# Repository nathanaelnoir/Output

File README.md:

# Output (KiCad 9)

Multi-sheet KiCad 9 project providing schematics and PCB for audio output / amplifier modules.

## Table of contents
- Overview
- Features
- Project layout
- Quick start
- Build & assembly notes
- Testing
- BOM
- Contributing
- License

## Overview
This repository contains the KiCad 9 project `output_pcb`. It includes multiple schematic sheets (HP amp, line amp, IO, volume meter, etc.) and a single PCB layout. All design files live under `kicad/`.

## Features
- Multi-sheet schematic architecture for modular subsystems.
- Single PCB layout in KiCad 9 format: `kicad/output_pcb.kicad_pcb`.
- Mix of through-hole and SMD parts (jacks, headers, op-amps, passives).

## Project layout
Project files:
- `kicad/output_pcb.kicad_pro` — KiCad project file
- `kicad/output_pcb.kicad_sch` — top-level schematic (hierarchical)
- `kicad/output_pcb.kicad_pcb` — PCB layout
- `kicad/output_pcb.kicad_prl` — plot/print settings

- `output/` — generated zipped gerbers and other fabrication outputs

Schematic sheets:
- `kicad/hp_amp.kicad_sch` — HP / amp sheet
- `kicad/line_amp.kicad_sch` — line amp sheet
- `kicad/io_board.kicad_sch` — IO / connectors
- `kicad/rear_board.kicad_sch` — rear panel / connectors
- `kicad/volume_meter.kicad_sch` — meter sheet

## Quick start
1. Install KiCad 9.
2. Open `kicad/output_pcb.kicad_pro`.
3. In Schematic Editor: run ERC and review results.
4. In PCB Editor: update PCB from schematic, then run DRC.
5. Generate fabrication outputs (Gerbers, drill, BOM, pick-and-place) as needed.

## Build & assembly notes
- Follow footprints and polarity/orientation markings (IC notches, electrolytics, LEDs, diodes).
- Suggested assembly order: SMD (reflow/paste) → THT (jacks, headers, pots) → mechanical fixtures.
- Decoupling: place 100 nF capacitors close to each op-amp’s power pins; use bulk electrolytics on rails where appropriate.
- Verify mechanical alignment (jack positions, mounting holes) against your panel/enclosure before final tightening.

## Testing
1. Power: apply power with no signal inputs; verify rail voltages and polarity at key ICs/connectors.
2. Signal: inject known signals; verify outputs with an oscilloscope or audio probe.
3. Mechanics: confirm jack seating, connector fit, and pot operation.

## BOM
The BOM is user-maintained in `BOM.md`. A KiCad-exported CSV can be generated from the schematic if you prefer a machine-readable BOM.

<details>
  <summary><strong>Detailed BOM</strong></summary>

### Bill of Materials

Please verify against the schematic before procurement.

Sanity-check totals (deduplicated):
- Capacitors (C): 34
- Diodes/LEDs (D): 12
- Mounting holes (H): 4
- Connectors/Jacks/Headers (J): 13
- Resistors (R): 48
- Pots (RV): 2
- ICs (U): 12
- Total line-item quantity: 125

Cleanup notes:
- Removed duplicate single entries for `C1` and `C2` (the combined `C1, C2` entry already covers them).
- `U2, U7, U10–U12`: datasheet link points to TL071 (not TL074). Consider updating the URL.
- `J12, J22`: footprint name contains repeated `P2.54mm`; confirm it matches your library.

### BOM table

| Designator(s) | Qty | Value / Part | Footprint | Vendor / URL | Notes |
|---|---:|---|---|---|---|
| C1, C2 | 2 | 150 nF | Capacitor_THT:C_Disc_D4.7mm_W2.5mm_P5.00mm | https://www.taydaelectronics.com/10-x-0-15uf-50v-ceramic-disc-capacitor-pkg-of-10.html | |
| C5–C28 | 24 | 100 nF | Capacitor_THT:C_Disc_D4.7mm_W2.5mm_P5.00mm | https://www.taydaelectronics.com/a-553-0-1uf-50v-ceramic-disc-capacitor-pkg-of-10.html | |
| C29, C30, C33, C34 | 4 | 100 pF | Capacitor_THT:C_Disc_D4.7mm_W2.5mm_P5.00mm | https://www.taydaelectronics.com/10-x-100pf-50v-ceramic-disc-capacitor-pkg-of-10.html | |
| C31, C32, C39, C40 | 4 | 10 µF | Capacitor_THT:CP_Radial_D4.0mm_P1.50mm | https://www.taydaelectronics.com/datasheets/files/A-3931.PDF | |
| D1, D2 | 2 | 1N4148 | Diode_THT:D_A-405_P7.62mm_Horizontal | https://www.taydaelectronics.com/datasheets/files/A-157.PDF | |
| D3, D8 | 2 | LED (RED) 3mm | LED_THT:LED_D3.0mm_Clear | https://www.taydaelectronics.com/led-3mm-red-water-clear-ultra-bright.html | |
| D4, D9 | 2 | LED (AMBER) 3mm | LED_THT:LED_D3.0mm_Clear | https://www.taydaelectronics.com/led-3mm-orange-water-clear.html | |
| D5–D7, D10–D12 | 6 | LED (GREEN) 3mm | LED_THT:LED_D3.0mm_Clear | https://www.taydaelectronics.com/led-3mm-green-water-clear-super-bright.html | |
| H1–H4 | 4 | Mounting Hole 2.7mm | MountingHole:MountingHole_2.7mm_M2.5 | — | |
| J1, J2 | 2 | 3.5 mm Audio Jack (switching) | Eurorack:Jack_3.5mm_QingPu_WQP-PJ398SM_Vertical | https://www.taydaelectronics.com/datasheets/files/w-qp-518ma_drawings.pdf | |
| J3–J5 | 3 | 6.35 mm Audio Jack | Eurorack:Jack_6.35mm_PJ_629HAN_slots | https://www.taydaelectronics.com/datasheets/files/A-1121.pdf | |
| J6 | 1 | 2x5 Eurorack power header | Connector_IDC:IDC-Header_2x05_P2.54mm_Vertical | https://www.taydaelectronics.com/datasheets/files/A-2939.pdf | |
| J7 | 1 | 1x3 Pin Socket | Connector_PinHeader_2.54mm:PinHeader_1x03_P2.54mm_Vertical | https://www.taydaelectronics.com/datasheets/files/FH411.pdf | |
| J11, J13, J21, J23 | 4 | 1x10 Pin Header | Connector_PinHeader_2.54mm:PinHeader_1x10_P2.54mm_Vertical | https://www.taydaelectronics.com/datasheets/files/A-197.pdf | |
| J12, J22 | 2 | 1x10 Pin Socket | Connector_PinHeader_2.54mm:PinHeader_1x10_P2.54mm_P2.54mm_Vertical | https://www.taydaelectronics.com/datasheets/files/FH411.pdf | |
| R1, R2 | 2 | 100 kΩ | Resistor_THT:R_Axial_DIN0207_L6.3mm_D2.5mm_P10.16mm_Horizontal | reichelt | |
| R3, R11, R19, R20 | 4 | 20 kΩ | Resistor_THT:R_Axial_DIN0207_L6.3mm_D2.5mm_P10.16mm_Horizontal | https://www.taydaelectronics.com/datasheets/files/royalohmprecisionmetalmf.pdf | |
| R4–R6, R12–R14, R21–R26, R39–R48 | 22 | 10 kΩ | Resistor_THT:R_Axial_DIN0207_L6.3mm_D2.5mm_P10.16mm_Horizontal | https://www.taydaelectronics.com/datasheets/files/royalohmprecisionmetalmf.pdf | |
| R7–R10, R15–R18 | 8 | 10 Ω | Resistor_THT:R_Axial_DIN0207_L6.3mm_D2.5mm_P10.16mm_P10.16mm_Horizontal | reichelt | footprint string differs; verify |
| R27–R30 | 4 | 100 Ω | Resistor_THT:R_Axial_DIN0207_L6.3mm_D2.5mm_P10.16mm_Horizontal | reichelt | |
| R31, R32 | 2 | 22 kΩ | Resistor_THT:R_Axial_DIN0207_L6.3mm_D2.5mm_P10.16mm_Horizontal | reichelt | |
| R33 | 1 | 33 kΩ | Resistor_THT:R_Axial_DIN0207_L6.3mm_D2.5mm_P10.16mm_Horizontal | reichelt | |
| R34 | 1 | 2.2 kΩ | Resistor_THT:R_Axial_DIN0207_L6.3mm_D2.5mm_P10.16mm_Horizontal | reichelt | |
| R35 | 1 | 1.5 kΩ | Resistor_THT:R_Axial_DIN0207_L6.3mm_D2.5mm_P10.16mm_Horizontal | https://www.taydaelectronics.com/datasheets/files/royalohmprecisionmetalmf.pdf | |
| R36 | 1 | 2.4 kΩ | Resistor_THT:R_Axial_DIN0207_L6.3mm_D2.5mm_P10.16mm_Horizontal | https://www.taydaelectronics.com/datasheets/files/royalohmprecisionmetalmf.pdf | |
| R37 | 1 | 820 Ω | Resistor_THT:R_Axial_DIN0207_L6.3mm_D2.5mm_P10.16mm_Horizontal | https://www.taydaelectronics.com/datasheets/files/royalohmprecisionmetalmf.pdf | |
| R38 | 1 | 470 Ω | Resistor_THT:R_Axial_DIN0207_L6.3mm_D2.5mm_P10.16mm_Horizontal | reichelt | |
| RV1, RV2 | 2 | 50 kΩ B (potentiometer) | Eurorack:Potentiometer_Alpha_RD902F-40-00D_Dual_Vertical_CircularHoles_centered | https://www.taydaelectronics.com/datasheets/files/A-5440.pdf | |
| U1 | 1 | TL072 (dual op-amp) | Package_DIP:DIP-8_W7.62mm | reichelt | |
| U2, U7, U10–U12 | 5 | TL074 (quad op-amp) | Package_DIP:DIP-14_W7.62mm | http://www.ti.com/lit/ds/symlink/tl071.pdf | datasheet link likely for TL074 |
| U3–U6, U8, U9 | 6 | NE5532 (dual op-amp) | Package_DIP:DIP-8_W7.62mm | https://www.taydaelectronics.com/ne5532-5532-ic-dual-low-noise-op-amp.html | |

</details>

## Contributing
Issues and PRs welcome. If you change schematics/PCB, include updated BOM and any relevant build/test notes.

## License
MIT — see `LICENSE`.

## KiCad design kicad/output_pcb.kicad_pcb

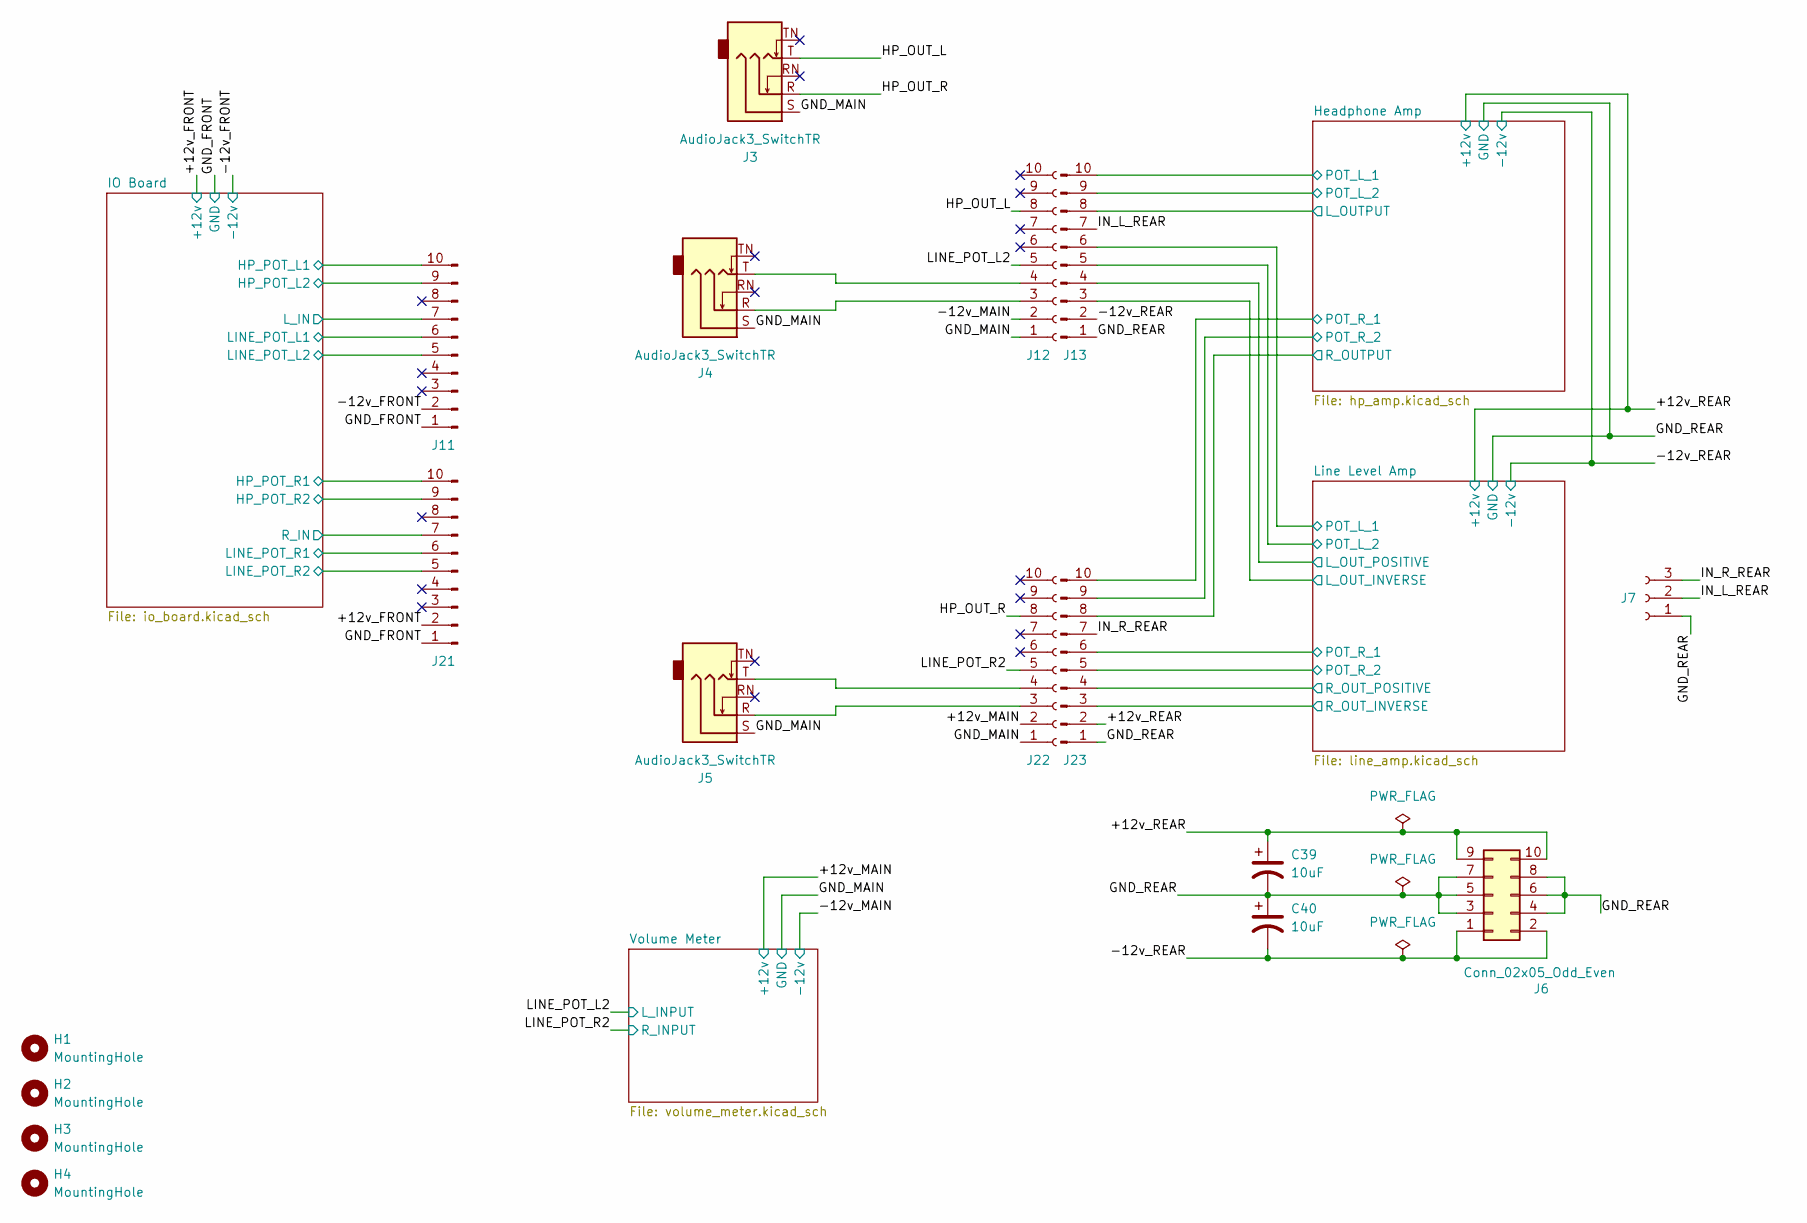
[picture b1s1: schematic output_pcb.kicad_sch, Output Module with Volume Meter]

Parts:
C39, C40: 10uF; CP_Radial_D4.0mm_P1.50mm
H1, H2, H3, H4: MountingHole; MountingHole_2.7mm_M2.5
J3, J4, J5: AudioJack3_SwitchTR; Jack_6.35mm_PJ_629HAN_slots
J6: Conn_02x05_Odd_Even; IDC-Header_2x05_P2.54mm_Vertical
J7: Conn_01x03_Socket; PinHeader_1x03_P2.54mm_Vertical
J11, J13, J21, J23: Conn_01x10_Pin; PinHeader_1x10_P2.54mm_Vertical
J12, J22: Conn_01x10_Socket; PinHeader_1x10_P2.54mm_Vertical

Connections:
/+12v_FRONT: J21.2; also elsewhere on the board
/+12v_MAIN: J22.2; also elsewhere on the board
/+12v_REAR: C39.1, J6.9, J6.10, J23.2; also elsewhere on the board
/-12v_FRONT: J11.2; also elsewhere on the board
/-12v_MAIN: J12.2; also elsewhere on the board
/-12v_REAR: C40.2, J6.1, J6.2, J13.2; also elsewhere on the board
/GND_FRONT: J11.1, J21.1; also elsewhere on the board
/GND_MAIN: J3.S, J4.S, J5.S, J12.1, J22.1; also elsewhere on the board
/GND_REAR: C39.2, C40.1, J6.3, J6.4, J6.5, J6.6, J6.7, J6.8, J7.1, J13.1, J23.1; also elsewhere on the board
/HP_OUT_L: J3.T, J12.8
/HP_OUT_R: J3.R, J22.8
/Headphone Amp/L_OUTPUT: J13.8; also elsewhere on the board
/Headphone Amp/POT_L_1: J13.10; also elsewhere on the board
/Headphone Amp/POT_L_2: J13.9; also elsewhere on the board
/Headphone Amp/POT_R_1: J23.10; also elsewhere on the board
/Headphone Amp/POT_R_2: J23.9; also elsewhere on the board
/Headphone Amp/R_OUTPUT: J23.8; also elsewhere on the board
/IN_L_REAR: J7.2, J13.7
/IN_R_REAR: J7.3, J23.7
/IO Board/HP_POT_L1: J11.10; also elsewhere on the board
/IO Board/HP_POT_L2: J11.9; also elsewhere on the board
/IO Board/HP_POT_R1: J21.10; also elsewhere on the board
/IO Board/HP_POT_R2: J21.9; also elsewhere on the board
/IO Board/LINE_POT_L1: J11.6; also elsewhere on the board
/IO Board/LINE_POT_L2: J11.5; also elsewhere on the board
/IO Board/LINE_POT_R1: J21.6; also elsewhere on the board
/IO Board/LINE_POT_R2: J21.5; also elsewhere on the board
/IO Board/L_IN: J11.7; also elsewhere on the board
/IO Board/R_IN: J21.7; also elsewhere on the board
/LINE_POT_L2: J12.5; also elsewhere on the board
/LINE_POT_R2: J22.5; also elsewhere on the board
/Line Level Amp/L_OUT_INVERSE: J13.3; also elsewhere on the board
/Line Level Amp/L_OUT_POSITIVE: J13.4; also elsewhere on the board
/Line Level Amp/POT_L_1: J13.6; also elsewhere on the board
/Line Level Amp/POT_L_2: J13.5; also elsewhere on the board
/Line Level Amp/POT_R_1: J23.6; also elsewhere on the board
/Line Level Amp/POT_R_2: J23.5; also elsewhere on the board
/Line Level Amp/R_OUT_INVERSE: J23.3; also elsewhere on the board
/Line Level Amp/R_OUT_POSITIVE: J23.4; also elsewhere on the board
unnamed: J4.R, J12.3
unnamed: J4.T, J12.4
unnamed: J5.R, J22.3
unnamed: J5.T, J22.4

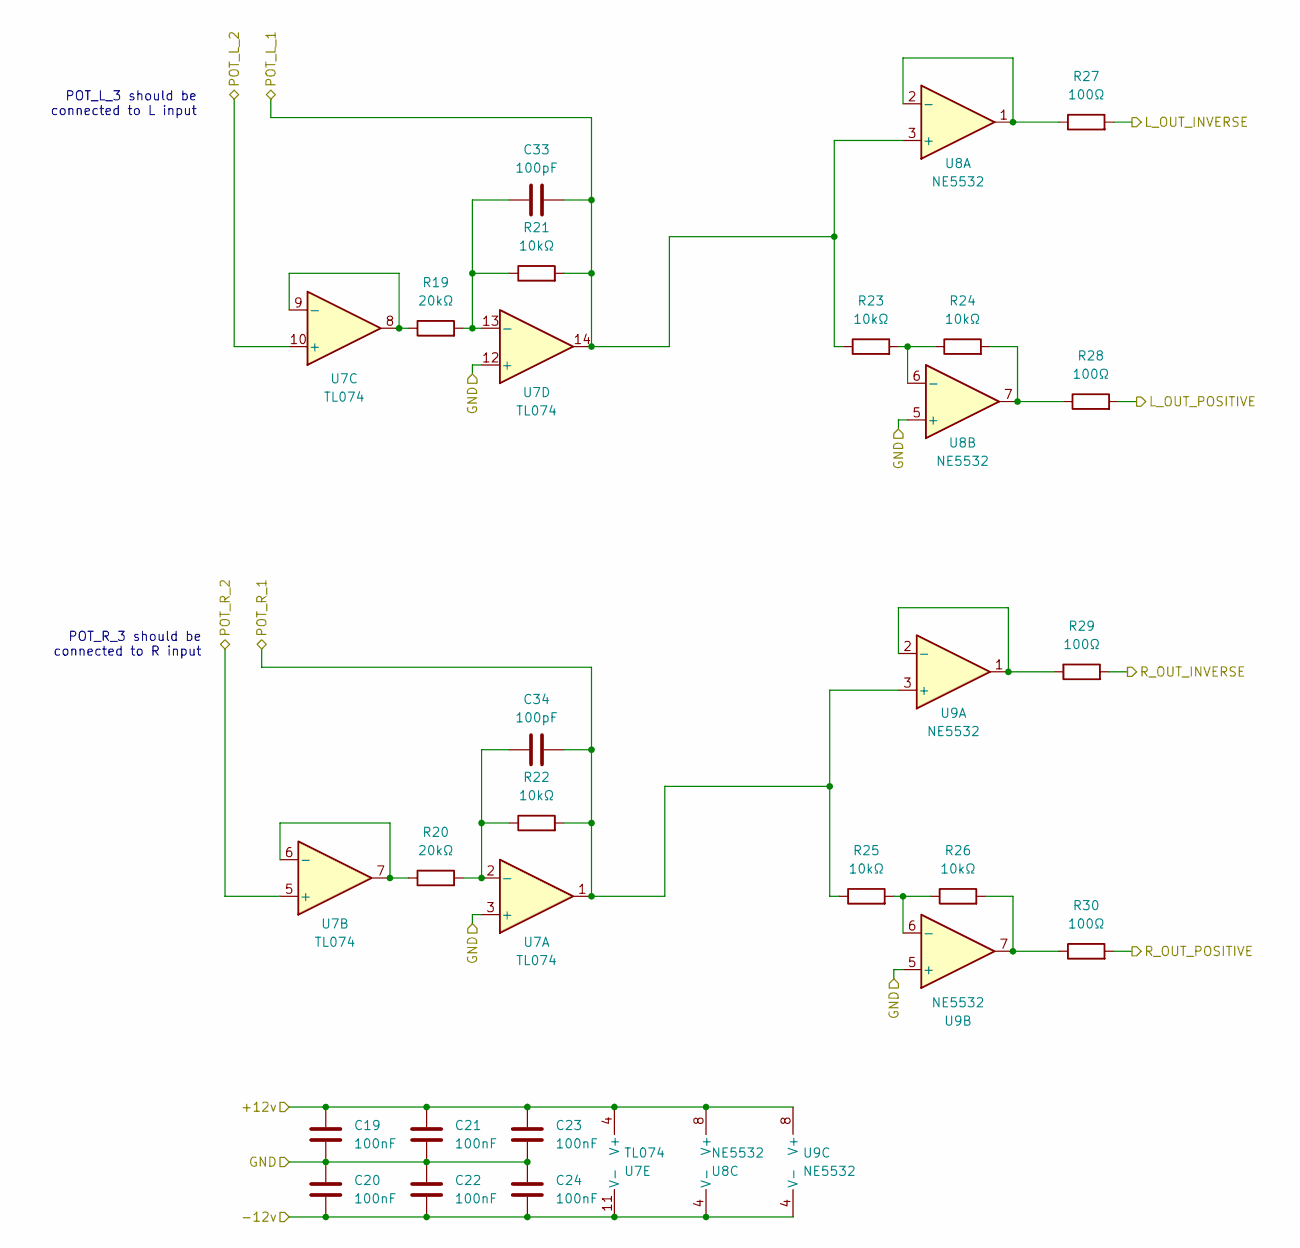
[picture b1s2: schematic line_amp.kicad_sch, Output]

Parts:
C19, C20, C21, C22, C23, C24: 100nF; C_Disc_D4.7mm_W2.5mm_P5.00mm
C33, C34: 100pF; C_Disc_D4.7mm_W2.5mm_P5.00mm
R19, R20: 20kΩ; R_Axial_DIN0207_L6.3mm_D2.5mm_P10.16mm_Horizontal
R21, R22, R23, R24, R25, R26: 10kΩ; R_Axial_DIN0207_L6.3mm_D2.5mm_P10.16mm_Horizontal
R27, R28, R29, R30: 100Ω; R_Axial_DIN0207_L6.3mm_D2.5mm_P10.16mm_Horizontal
U7: TL074; DIP-14_W7.62mm
U8, U9: NE5532; DIP-8_W7.62mm

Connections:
/+12v_REAR: C19.2, C21.2, C23.2, U7.4 (V+), U8.8 (V+), U9.8 (V+); also elsewhere on the board
/-12v_REAR: C20.1, C22.1, C24.1, U7.11 (V-), U8.4 (V-), U9.4 (V-); also elsewhere on the board
/GND_REAR: C19.1, C20.2, C21.1, C22.2, C23.1, C24.2, U7.3 (+), U7.12 (+), U8.5 (+), U9.5 (+); also elsewhere on the board
/Line Level Amp/L_OUT_INVERSE: R27.2; also elsewhere on the board
/Line Level Amp/L_OUT_POSITIVE: R28.2; also elsewhere on the board
/Line Level Amp/POT_L_1: C33.2, R21.2, R23.1, U7.14, U8.3 (+); also elsewhere on the board
/Line Level Amp/POT_L_2: U7.10 (+); also elsewhere on the board
/Line Level Amp/POT_R_1: C34.2, R22.2, R25.1, U7.1, U9.3 (+); also elsewhere on the board
/Line Level Amp/POT_R_2: U7.5 (+); also elsewhere on the board
/Line Level Amp/R_OUT_INVERSE: R29.2; also elsewhere on the board
/Line Level Amp/R_OUT_POSITIVE: R30.2; also elsewhere on the board
unnamed: R24.2, R28.1, U8.7
unnamed: R26.2, R30.1, U9.7
unnamed: C34.1, R20.2, R22.1, U7.2 (-)
unnamed: R20.1, U7.6 (-), U7.7
unnamed: R19.1, U7.8, U7.9 (-)
unnamed: C33.1, R19.2, R21.1, U7.13 (-)
unnamed: R27.1, U8.1, U8.2 (-)
unnamed: R23.2, R24.1, U8.6 (-)
unnamed: R29.1, U9.1, U9.2 (-)
unnamed: R25.2, R26.1, U9.6 (-)

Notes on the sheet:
POT_R_3 should be connected to R input
POT_L_3 should be connected to L input

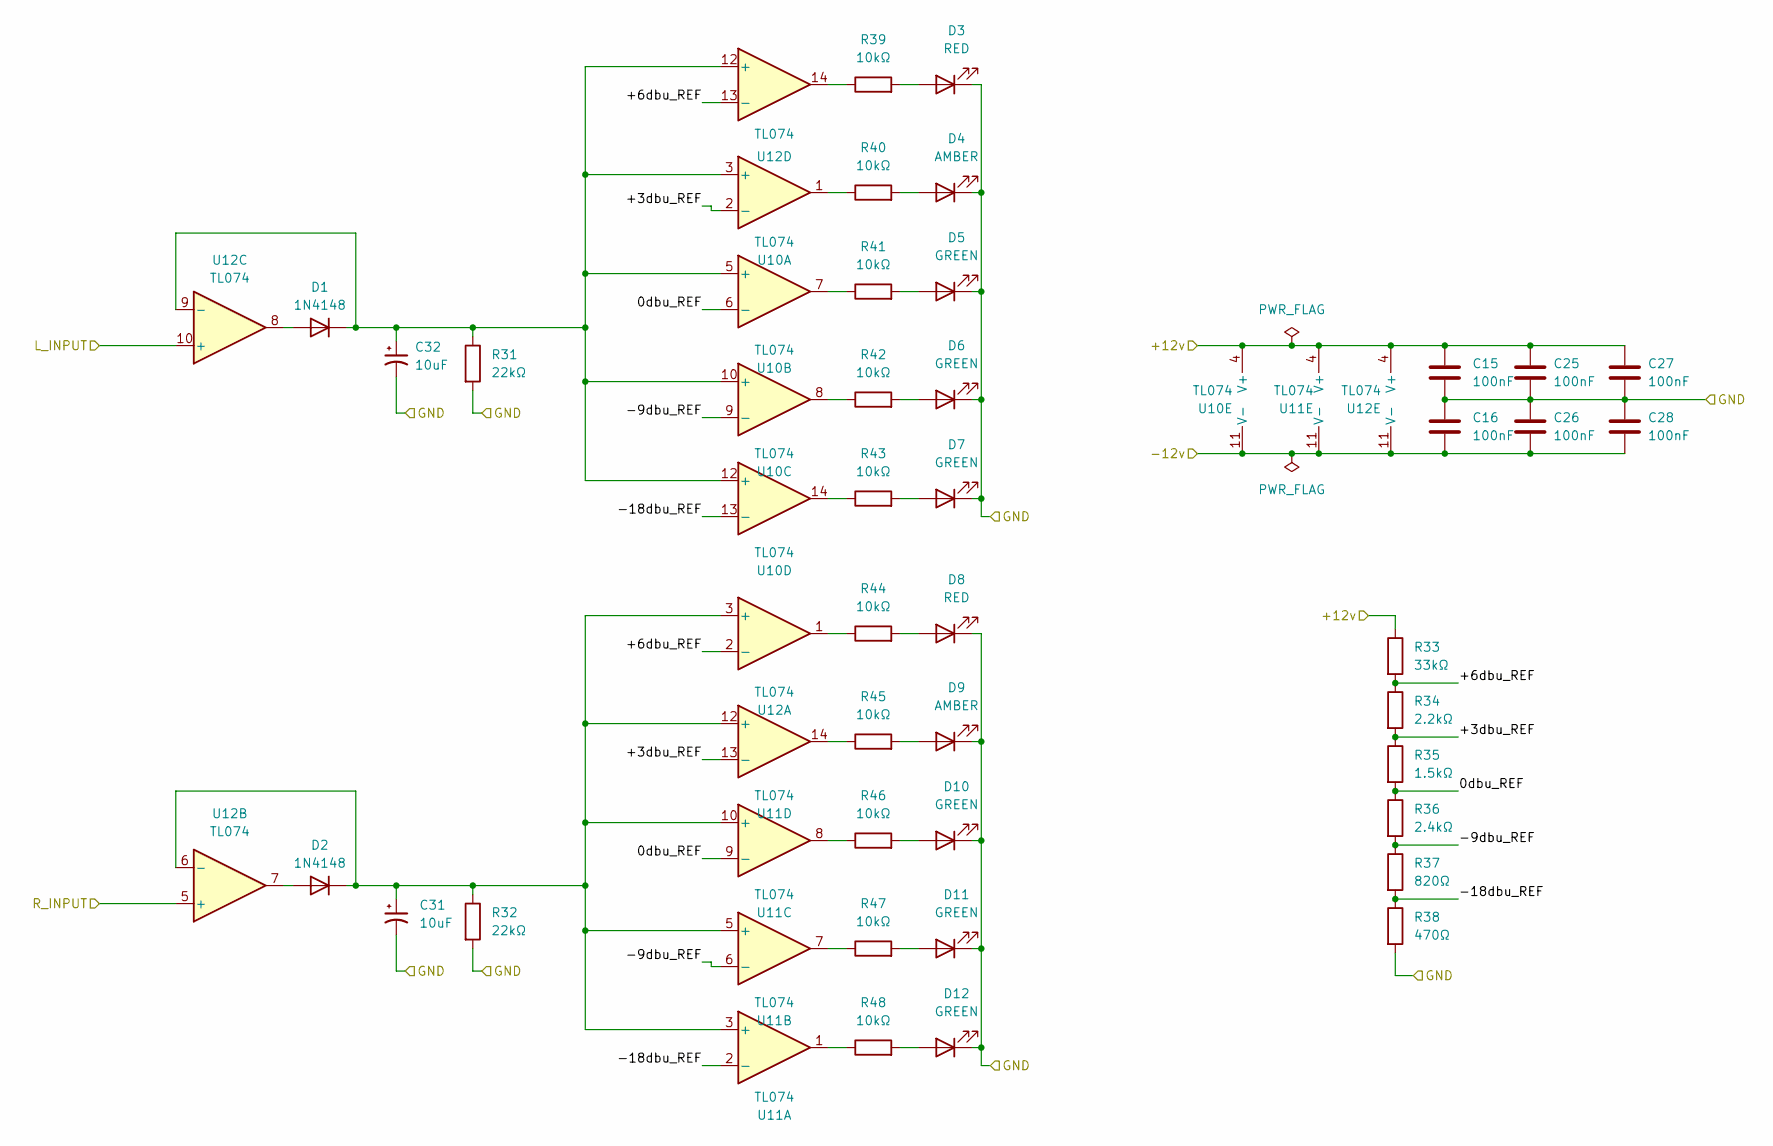
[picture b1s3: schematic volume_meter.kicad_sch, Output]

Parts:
C15, C16, C25, C26, C27, C28: 100nF; C_Disc_D4.7mm_W2.5mm_P5.00mm
C31, C32: 10uF; CP_Radial_D4.0mm_P1.50mm
D1, D2: 1N4148; D_A-405_P7.62mm_Horizontal
D3, D8: RED; LED_D3.0mm_Clear
D4, D9: AMBER; LED_D3.0mm_Clear
D5, D6, D7, D10, D11, D12: GREEN; LED_D3.0mm_Clear
R31, R32: 22kΩ; R_Axial_DIN0207_L6.3mm_D2.5mm_P10.16mm_Horizontal
R33: 33kΩ; R_Axial_DIN0207_L6.3mm_D2.5mm_P10.16mm_Horizontal
R34: 2.2kΩ; R_Axial_DIN0207_L6.3mm_D2.5mm_P10.16mm_Horizontal
R35: 1.5kΩ; R_Axial_DIN0207_L6.3mm_D2.5mm_P10.16mm_Horizontal
R36: 2.4kΩ; R_Axial_DIN0207_L6.3mm_D2.5mm_P10.16mm_Horizontal
R37: 820Ω; R_Axial_DIN0207_L6.3mm_D2.5mm_P10.16mm_Horizontal
R38: 470Ω; R_Axial_DIN0207_L6.3mm_D2.5mm_P10.16mm_Horizontal
R39, R40, R41, R42, R43, R44, R45, R46, R47, R48: 10kΩ; R_Axial_DIN0207_L6.3mm_D2.5mm_P10.16mm_Horizontal
U10, U11, U12: TL074; DIP-14_W7.62mm

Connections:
/+12v_MAIN: C15.1, C25.1, C27.1, R33.1, U10.4 (V+), U11.4 (V+), U12.4 (V+); also elsewhere on the board
/-12v_MAIN: C16.2, C26.2, C28.2, U10.11 (V-), U11.11 (V-), U12.11 (V-); also elsewhere on the board
/GND_MAIN: C15.2, C16.1, C25.2, C26.1, C27.2, C28.1, C31.2, C32.2, D3.1 (K), D4.1 (K), D5.1 (K), D6.1 (K), D7.1 (K), D8.1 (K), D9.1 (K), D10.1 (K), D11.1 (K), D12.1 (K), R31.2, R32.2, R38.2; also elsewhere on the board
/LINE_POT_L2: U12.10 (+); also elsewhere on the board
/LINE_POT_R2: U12.5 (+); also elsewhere on the board
/Volume Meter/0dbu_REF: R35.2, R36.1, U10.6 (-), U11.9 (-)
/Volume Meter/+3dbu_REF: R34.2, R35.1, U10.2 (-), U11.13 (-)
/Volume Meter/+6dbu_REF: R33.2, R34.1, U12.2 (-), U12.13 (-)
/Volume Meter/-9dbu_REF: R36.2, R37.1, U10.9 (-), U11.6 (-)
/Volume Meter/-18dbu_REF: R37.2, R38.1, U10.13 (-), U11.2 (-)
unnamed: D1.2 (A), U12.8
unnamed: C32.1, D1.1 (K), R31.1, U10.3 (+), U10.5 (+), U10.10 (+), U10.12 (+), U12.9 (-), U12.12 (+)
unnamed: D2.2 (A), U12.7
unnamed: C31.1, D2.1 (K), R32.1, U11.3 (+), U11.5 (+), U11.10 (+), U11.12 (+), U12.3 (+), U12.6 (-)
unnamed: D3.2 (A), R39.2
unnamed: D4.2 (A), R40.2
unnamed: D5.2 (A), R41.2
unnamed: D6.2 (A), R42.2
unnamed: D7.2 (A), R43.2
unnamed: D8.2 (A), R44.2
unnamed: D9.2 (A), R45.2
unnamed: D10.2 (A), R46.2
unnamed: D11.2 (A), R47.2
unnamed: D12.2 (A), R48.2
unnamed: R39.1, U12.14
unnamed: R40.1, U10.1
unnamed: R41.1, U10.7
unnamed: R42.1, U10.8
unnamed: R43.1, U10.14
unnamed: R44.1, U12.1
unnamed: R45.1, U11.14
unnamed: R46.1, U11.8
unnamed: R47.1, U11.7
unnamed: R48.1, U11.1

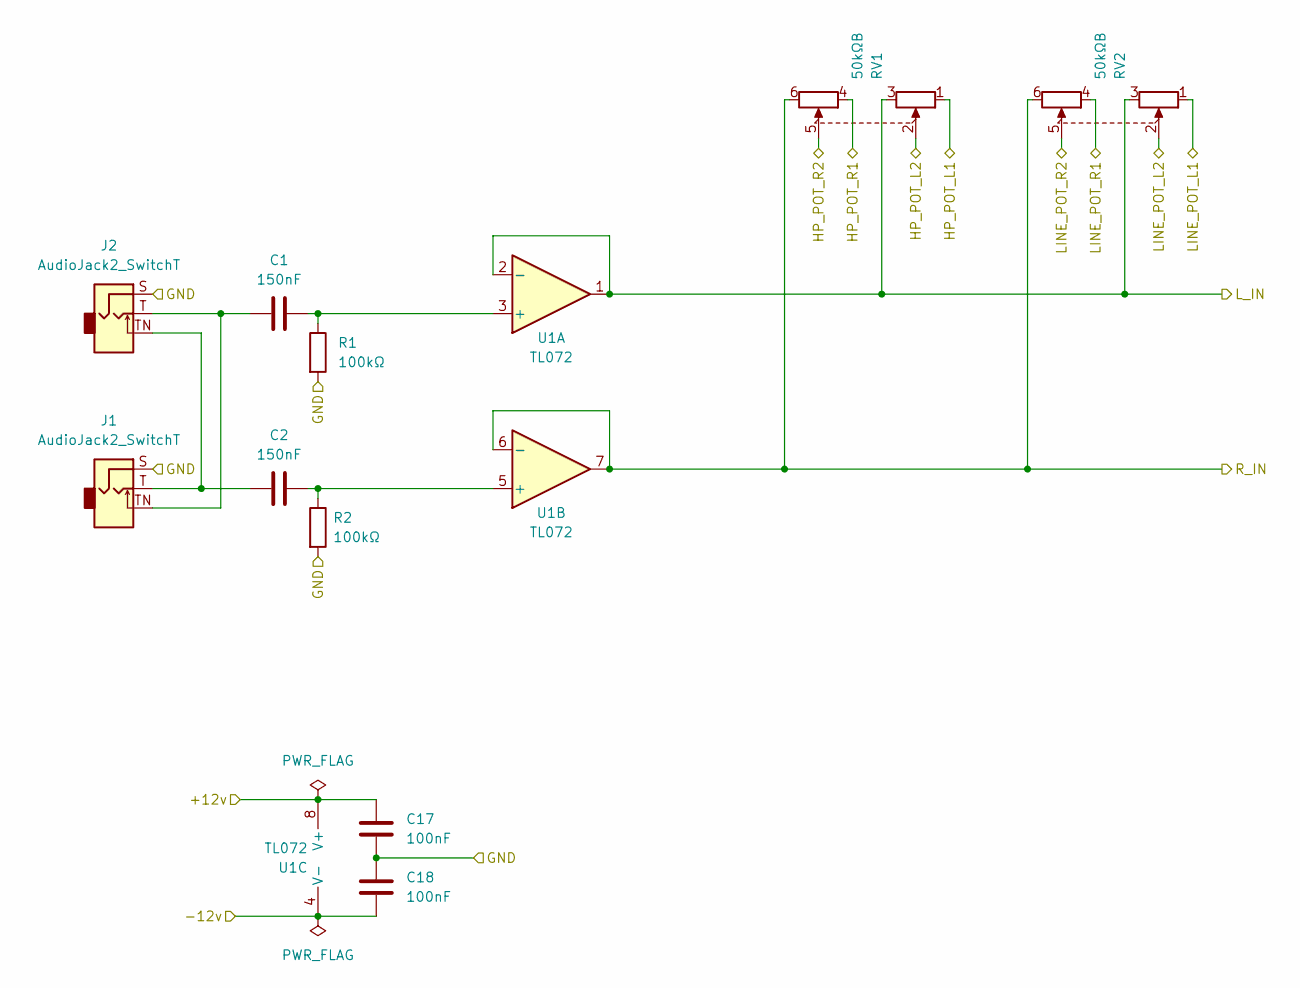
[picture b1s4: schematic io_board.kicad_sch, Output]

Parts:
C1, C2: 150nF; C_Disc_D4.7mm_W2.5mm_P5.00mm
C17, C18: 100nF; C_Disc_D4.7mm_W2.5mm_P5.00mm
J1, J2: AudioJack2_SwitchT; Jack_3.5mm_QingPu_WQP-PJ398SM_Vertical
R1, R2: 100kΩ; R_Axial_DIN0207_L6.3mm_D2.5mm_P10.16mm_Horizontal
RV1, RV2: 50kΩB; Potentiometer_Alpha_RD902F-40-00D_Dual_Vertical_CircularHol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
U1: TL072; DIP-8_W7.62mm

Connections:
/+12v_FRONT: C17.1, U1.8 (V+); also elsewhere on the board
/-12v_FRONT: C18.2, U1.4 (V-); also elsewhere on the board
/GND_FRONT: C17.2, C18.1, J1.S, J2.S, R1.2, R2.2; also elsewhere on the board
/IO Board/HP_POT_L1: RV1.1; also elsewhere on the board
/IO Board/HP_POT_L2: RV1.2; also elsewhere on the board
/IO Board/HP_POT_R1: RV1.4; also elsewhere on the board
/IO Board/HP_POT_R2: RV1.5; also elsewhere on the board
/IO Board/LINE_POT_L1: RV2.1; also elsewhere on the board
/IO Board/LINE_POT_L2: RV2.2; also elsewhere on the board
/IO Board/LINE_POT_R1: RV2.4; also elsewhere on the board
/IO Board/LINE_POT_R2: RV2.5; also elsewhere on the board
/IO Board/L_IN: RV1.3, RV2.3, U1.1, U1.2 (-); also elsewhere on the board
/IO Board/R_IN: RV1.6, RV2.6, U1.6 (-), U1.7; also elsewhere on the board
unnamed: C1.1, J1.TN, J2.T
unnamed: C2.1, J1.T, J2.TN
unnamed: C1.2, R1.1, U1.3 (+)
unnamed: C2.2, R2.1, U1.5 (+)

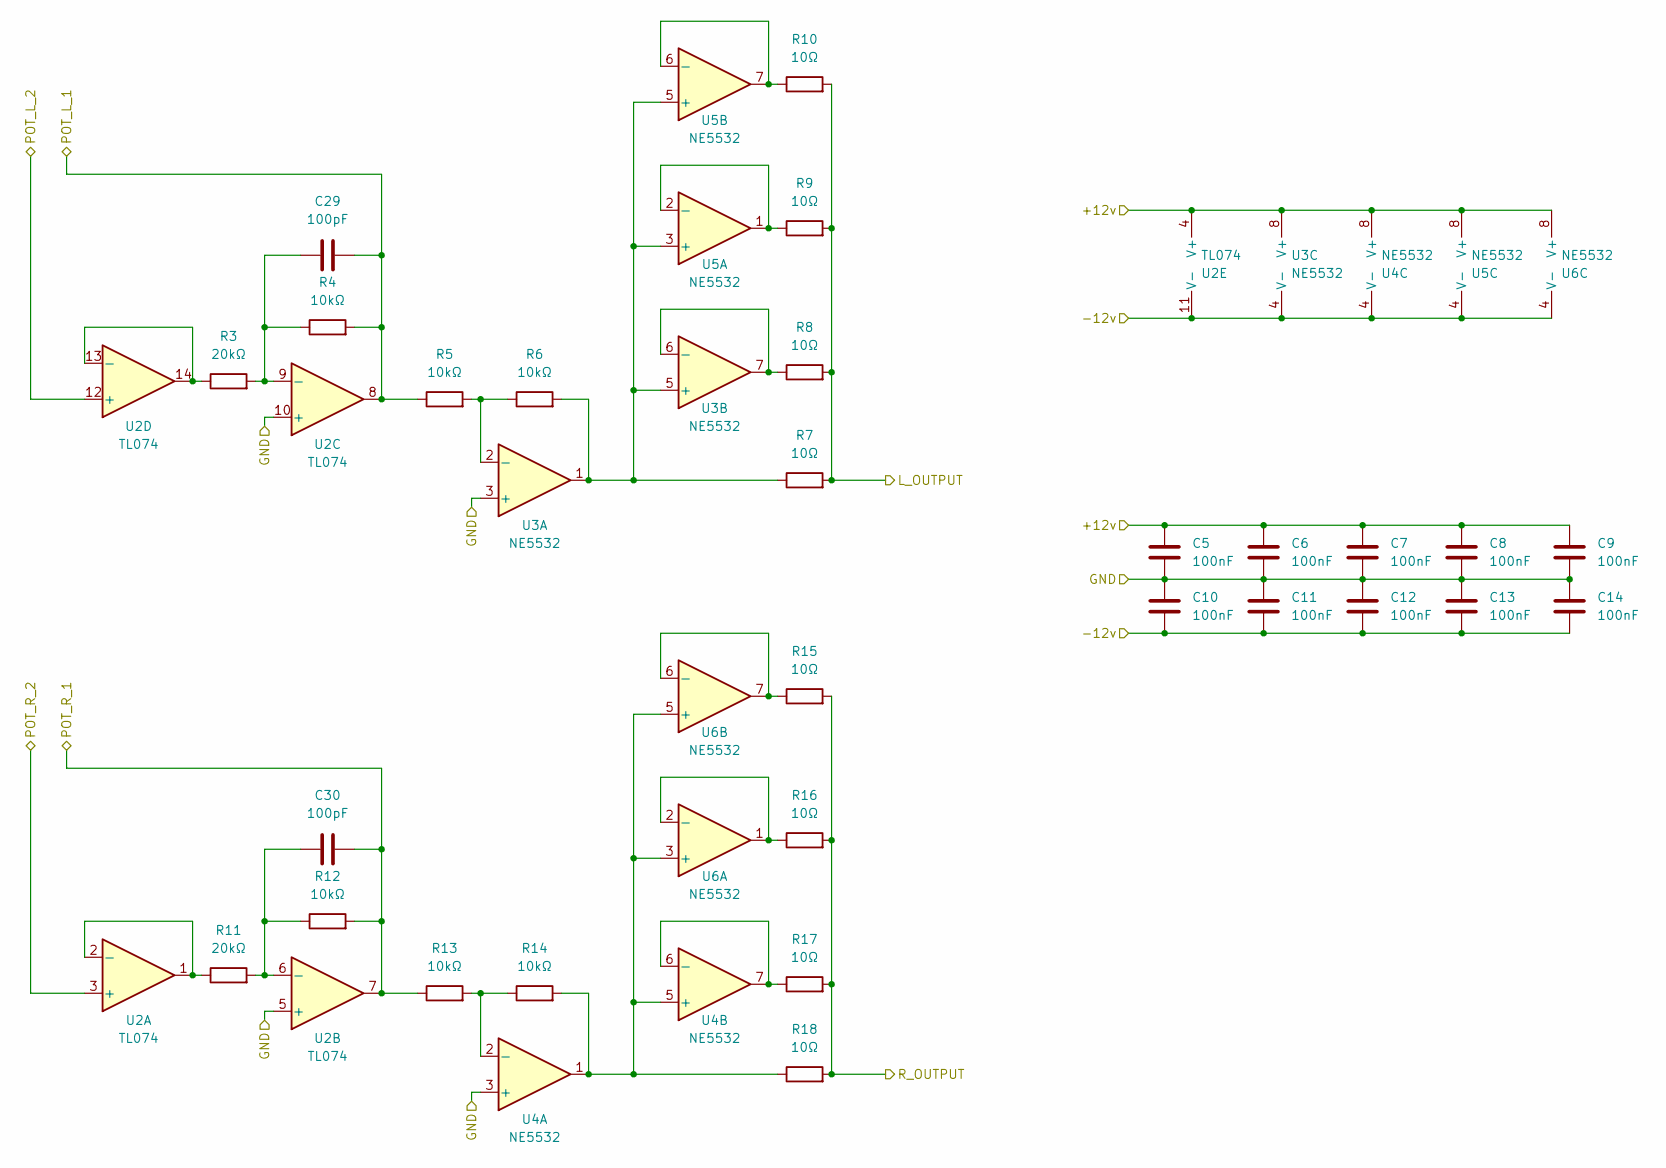
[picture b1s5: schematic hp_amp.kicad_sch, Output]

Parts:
C5, C6, C7, C8, C9, C10, C11, C12, C13, C14: 100nF; C_Disc_D4.7mm_W2.5mm_P5.00mm
C29, C30: 100pF; C_Disc_D4.7mm_W2.5mm_P5.00mm
R3, R11: 20kΩ; R_Axial_DIN0207_L6.3mm_D2.5mm_P10.16mm_Horizontal
R4, R5, R6, R12, R13, R14: 10kΩ; R_Axial_DIN0207_L6.3mm_D2.5mm_P10.16mm_Horizontal
R7, R8, R9, R10, R15, R16, R17, R18: 10Ω; R_Axial_DIN0207_L6.3mm_D2.5mm_P10.16mm_Horizontal
U2: TL074; DIP-14_W7.62mm
U3, U4, U5, U6: NE5532; DIP-8_W7.62mm

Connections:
/+12v_REAR: C5.2, C6.2, C7.2, C8.2, C9.2, U2.4 (V+), U3.8 (V+), U4.8 (V+), U5.8 (V+), U6.8 (V+); also elsewhere on the board
/-12v_REAR: C10.1, C11.1, C12.1, C13.1, C14.1, U2.11 (V-), U3.4 (V-), U4.4 (V-), U5.4 (V-), U6.4 (V-); also elsewhere on the board
/GND_REAR: C5.1, C6.1, C7.1, C8.1, C9.1, C10.2, C11.2, C12.2, C13.2, C14.2, U2.5 (+), U2.10 (+), U3.3 (+), U4.3 (+); also elsewhere on the board
/Headphone Amp/L_OUTPUT: R7.2, R8.2, R9.2, R10.2; also elsewhere on the board
/Headphone Amp/POT_L_1: C29.2, R4.2, R5.1, U2.8; also elsewhere on the board
/Headphone Amp/POT_L_2: U2.12 (+); also elsewhere on the board
/Headphone Amp/POT_R_1: C30.2, R12.2, R13.1, U2.7; also elsewhere on the board
/Headphone Amp/POT_R_2: U2.3 (+); also elsewhere on the board
/Headphone Amp/R_OUTPUT: R15.2, R16.2, R17.2, R18.2; also elsewhere on the board
unnamed: R11.1, U2.1, U2.2 (-)
unnamed: C30.1, R11.2, R12.1, U2.6 (-)
unnamed: C29.1, R3.2, R4.1, U2.9 (-)
unnamed: R3.1, U2.13 (-), U2.14
unnamed: R5.2, R6.1, U3.2 (-)
unnamed: R6.2, R7.1, U3.1, U3.5 (+), U5.3 (+), U5.5 (+)
unnamed: R8.1, U3.6 (-), U3.7
unnamed: R13.2, R14.1, U4.2 (-)
unnamed: R14.2, R18.1, U4.1, U4.5 (+), U6.3 (+), U6.5 (+)
unnamed: R17.1, U4.6 (-), U4.7
unnamed: R9.1, U5.1, U5.2 (-)
unnamed: R10.1, U5.6 (-), U5.7
unnamed: R16.1, U6.1, U6.2 (-)
unnamed: R15.1, U6.6 (-), U6.7

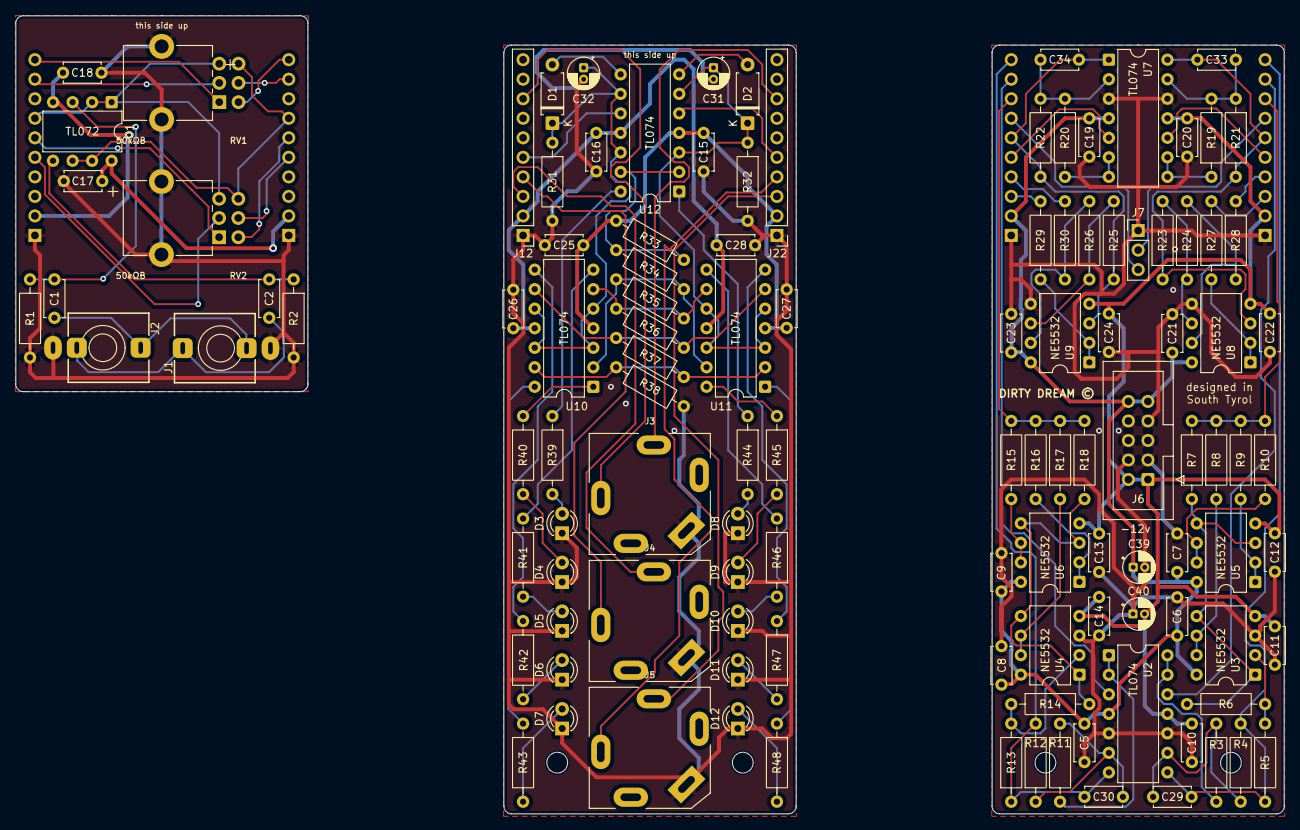
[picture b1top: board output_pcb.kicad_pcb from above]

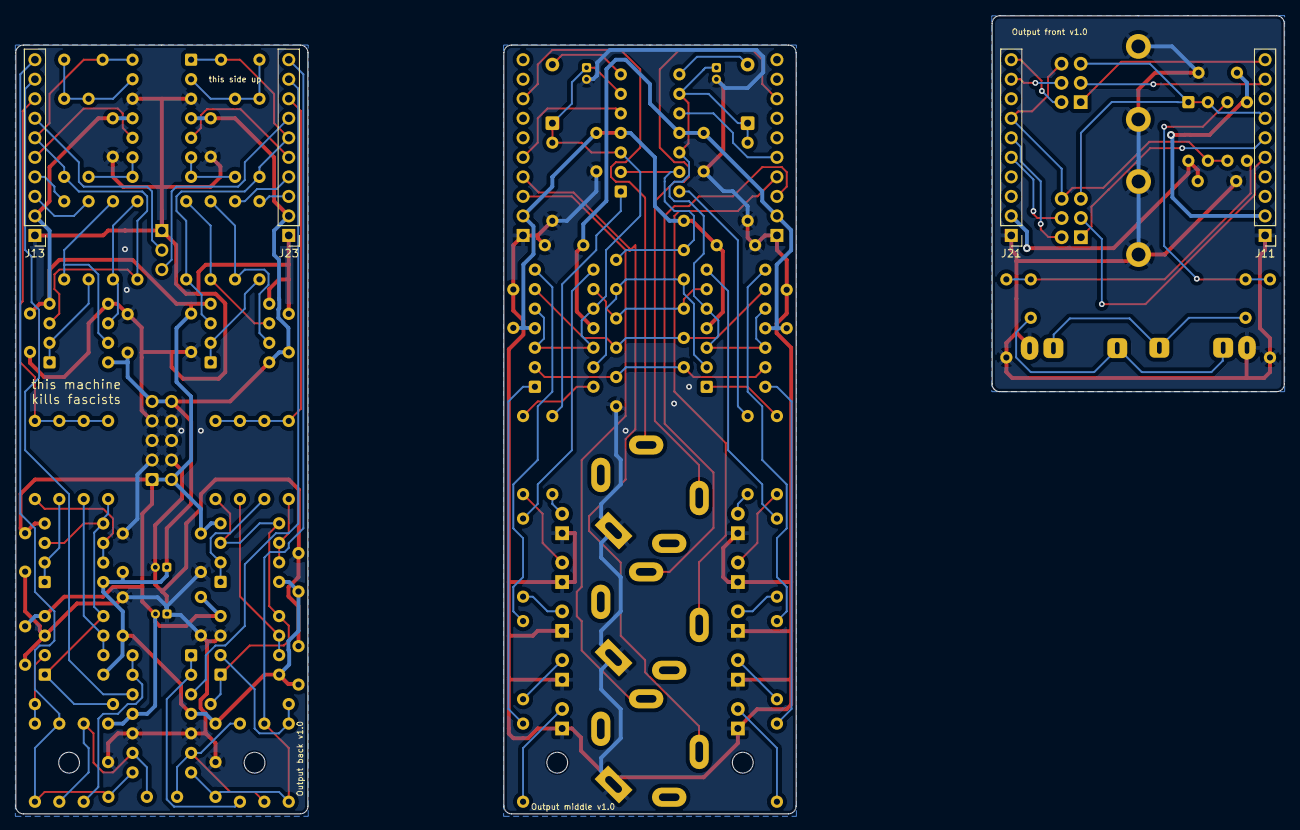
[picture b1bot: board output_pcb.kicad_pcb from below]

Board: 2 copper layers, 165.0 x 103.8 mm, 125 parts (4 on the bottom side), 100 nets.

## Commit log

2026-02-12 Refactor code structure for improved readability and maintainability
2026-02-12 Update KiCad project files and documentation
    - Changed active layer in output_pcb.kicad_prl from 5 to 0.
    - Updated project title, date, revision, and company in output_pcb.kicad_sch.
    - Modified footprint properties for jacks in output_pcb.kicad_sch to use "Eurorack" library.
    - Added README.md with project overview, features, quick start guide, file descriptions, build notes, testing procedures, and licensing information.
    - Created a lock file for the schematic output.
2026-02-12 Update PCB count in README to reflect the correct number of PCBs
2026-02-12 Update datasheet links in schematic files for accuracy and consistency
    - Updated multiple instances of the "Datasheet" property in io_board.kicad_sch to point to correct URLs for various components.
    - Revised datasheet links in line_amp.kicad_sch to ensure they direct to the appropriate product pages.
    - Corrected datasheet URLs in output_pcb.kicad_sch for several components to reflect the latest documentation.
    - Modified volume_meter.kicad_sch to replace outdated links with current datasheet URLs.
    - Removed lock file ~output_pcb.kicad_sch.lck as it is no longer needed.
2026-02-12 Update README to remove 'deduplicated' from Detailed BOM section
2026-02-12 rounded edges
2026-02-12 adding files in .gitignore
2026-02-12 adding Gerber files
2026-02-13 change of text
2026-02-13 Remove obsolete KiCad project file output_pcb.kicad_pro
2026-02-13 Update README.md: correct PCB count and add fabrication outputs section
2026-02-13 docs: add CONTRIBUTING guide and rename LICENSE to LICENSE.md - add CONTRIBUTING.md with contributor workflow and guidelines - rename LICENSE to LICENSE.md for markdown consistency
